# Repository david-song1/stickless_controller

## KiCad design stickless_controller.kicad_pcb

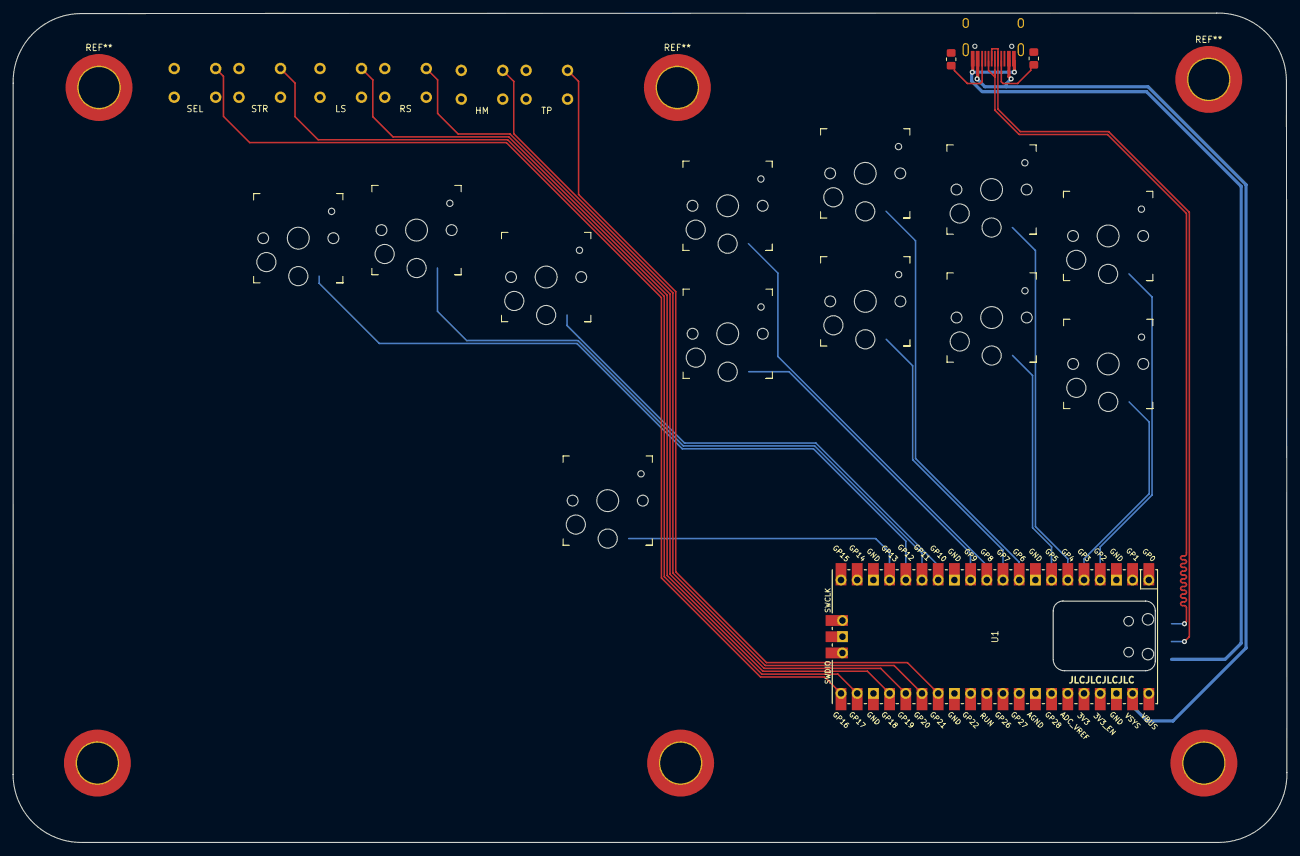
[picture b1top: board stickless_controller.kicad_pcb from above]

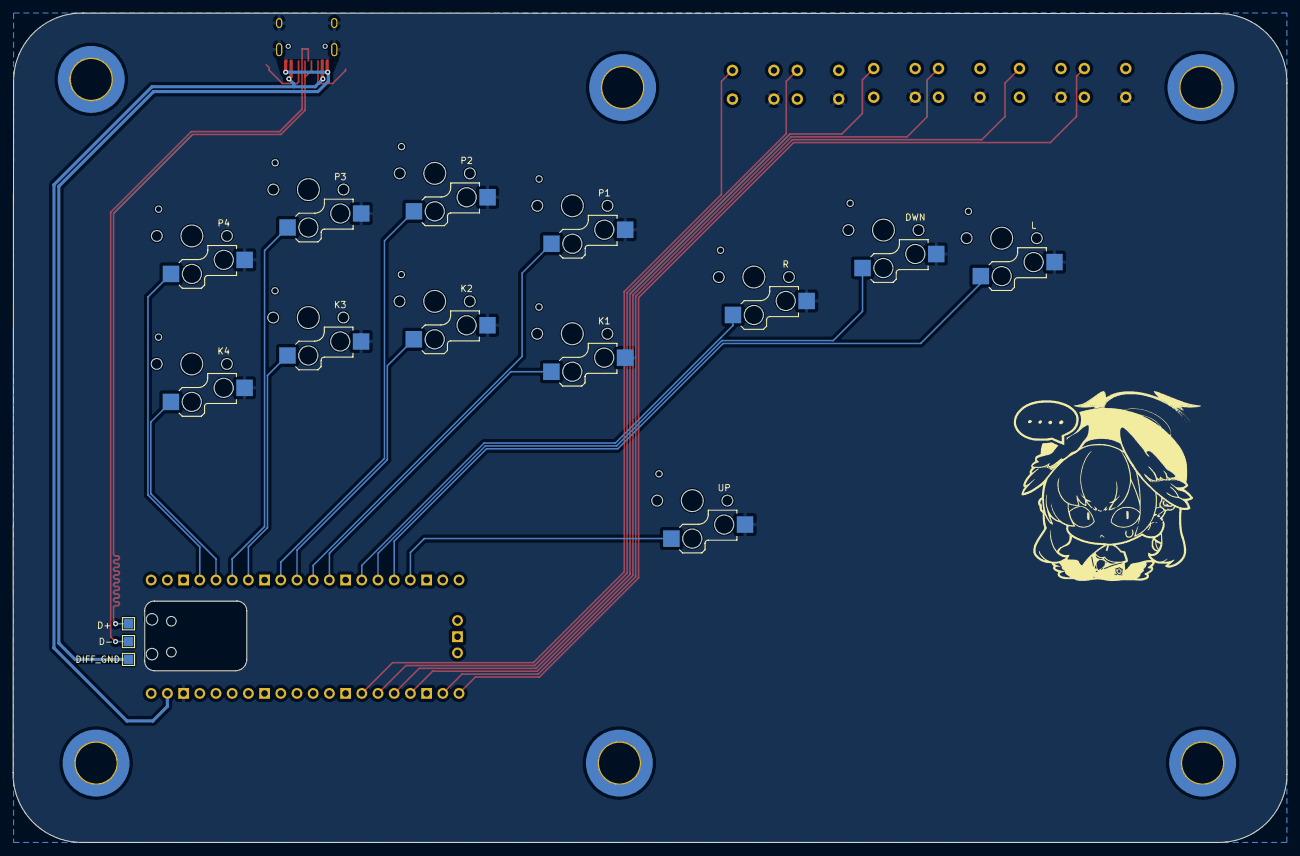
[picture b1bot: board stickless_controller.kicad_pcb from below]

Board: 2 copper layers, 199.7 x 130.0 mm, 25 parts (3 on the bottom side), 25 nets.

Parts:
D+: Conn_01x01; TestPoint_Pad_1.5x1.5mm
D-: Conn_01x01; TestPoint_Pad_1.5x1.5mm
DIFF_GND: Conn_01x01; TestPoint_Pad_1.5x1.5mm
DWN: MX-NoLED; Kailh_socket_PG1350
HM: SW_Push; PushButton_6x6mm_TH
K1, K2, K3, K4: MX-NoLED; Kailh_socket_PG1350
L: MX-NoLED; Kailh_socket_PG1350
LS: SW_Push; PushButton_6x6mm_TH
P1, P2, P3, P4: MX-NoLED; Kailh_socket_PG1350
R: MX-NoLED; Kailh_socket_PG1350
R1, R2: 5.1K; R_0805_2012Metric_Pad1.20x1.40mm_HandSolder
RS: SW_Push; PushButton_6x6mm_TH
SEL: SW_Push; PushButton_6x6mm_TH
STR: SW_Push; PushButton_6x6mm_TH
TP: SW_Push; PushButton_6x6mm_TH
U1: Pico; RPi_Pico_SMD_TH
UP: MX-NoLED; Kailh_socket_PG1350
USB1: HRO-TYPE-C-31-M-12; HRO-TYPE-C-31-M-12-HandSoldering

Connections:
GND: DWN.2 (ROW), HM.2, K1.2 (ROW), K2.2 (ROW), K3.2 (ROW), K4.2 (ROW), L.2 (ROW), LS.2, P1.2 (ROW), P2.2 (ROW), P3.2 (ROW), P4.2 (ROW), R.2 (ROW), R1.2, R2.2, RS.2, SEL.2, STR.2, TP.2, U1.38 (GND), UP.2 (ROW), USB1.13 (SHIELD)
GND1: DIFF_GND.1, USB1.1 (GND), USB1.12 (GND)
LS: LS.1, U1.24 (GPIO18)
unnamed: R2.1, USB1.4 (CC1)
unnamed: R1.1, USB1.10 (CC2)
RS: RS.1, U1.25 (GPIO19)
TP: TP.1, U1.27 (GPIO21)
VCC: U1.39 (VSYS), USB1.2 (VBUS), USB1.11 (VBUS)
d+: D+.1, USB1.6 (DP1), USB1.8 (DP2)
d-: D-.1, USB1.5 (DN2), USB1.7 (DN1)
down: DWN.1 (COL), U1.15 (GPIO11)
home: HM.1, U1.26 (GPIO20)
k1: K1.1 (COL), U1.12 (GPIO9)
k2: K2.1 (COL), U1.10 (GPIO7)
k3: K3.1 (COL), U1.7 (GPIO5)
k4: K4.1 (COL), U1.5 (GPIO3)
left: L.1 (COL), U1.16 (GPIO12)
p1: P1.1 (COL), U1.11 (GPIO8)
p2: P2.1 (COL), U1.9 (GPIO6)
p3: P3.1 (COL), U1.6 (GPIO4)
p4: P4.1 (COL), U1.4 (GPIO2)
right: R.1 (COL), U1.14 (GPIO10)
select: SEL.1, U1.21 (GPIO16)
start: STR.1, U1.22 (GPIO17)
up: U1.17 (GPIO13), UP.1 (COL)

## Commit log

2023-02-20 Added footprint libraries
2023-02-23 Finalized board layout
